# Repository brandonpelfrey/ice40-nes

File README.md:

# ice40-nes
NES implementation in a Lattice Ice40 FPGA

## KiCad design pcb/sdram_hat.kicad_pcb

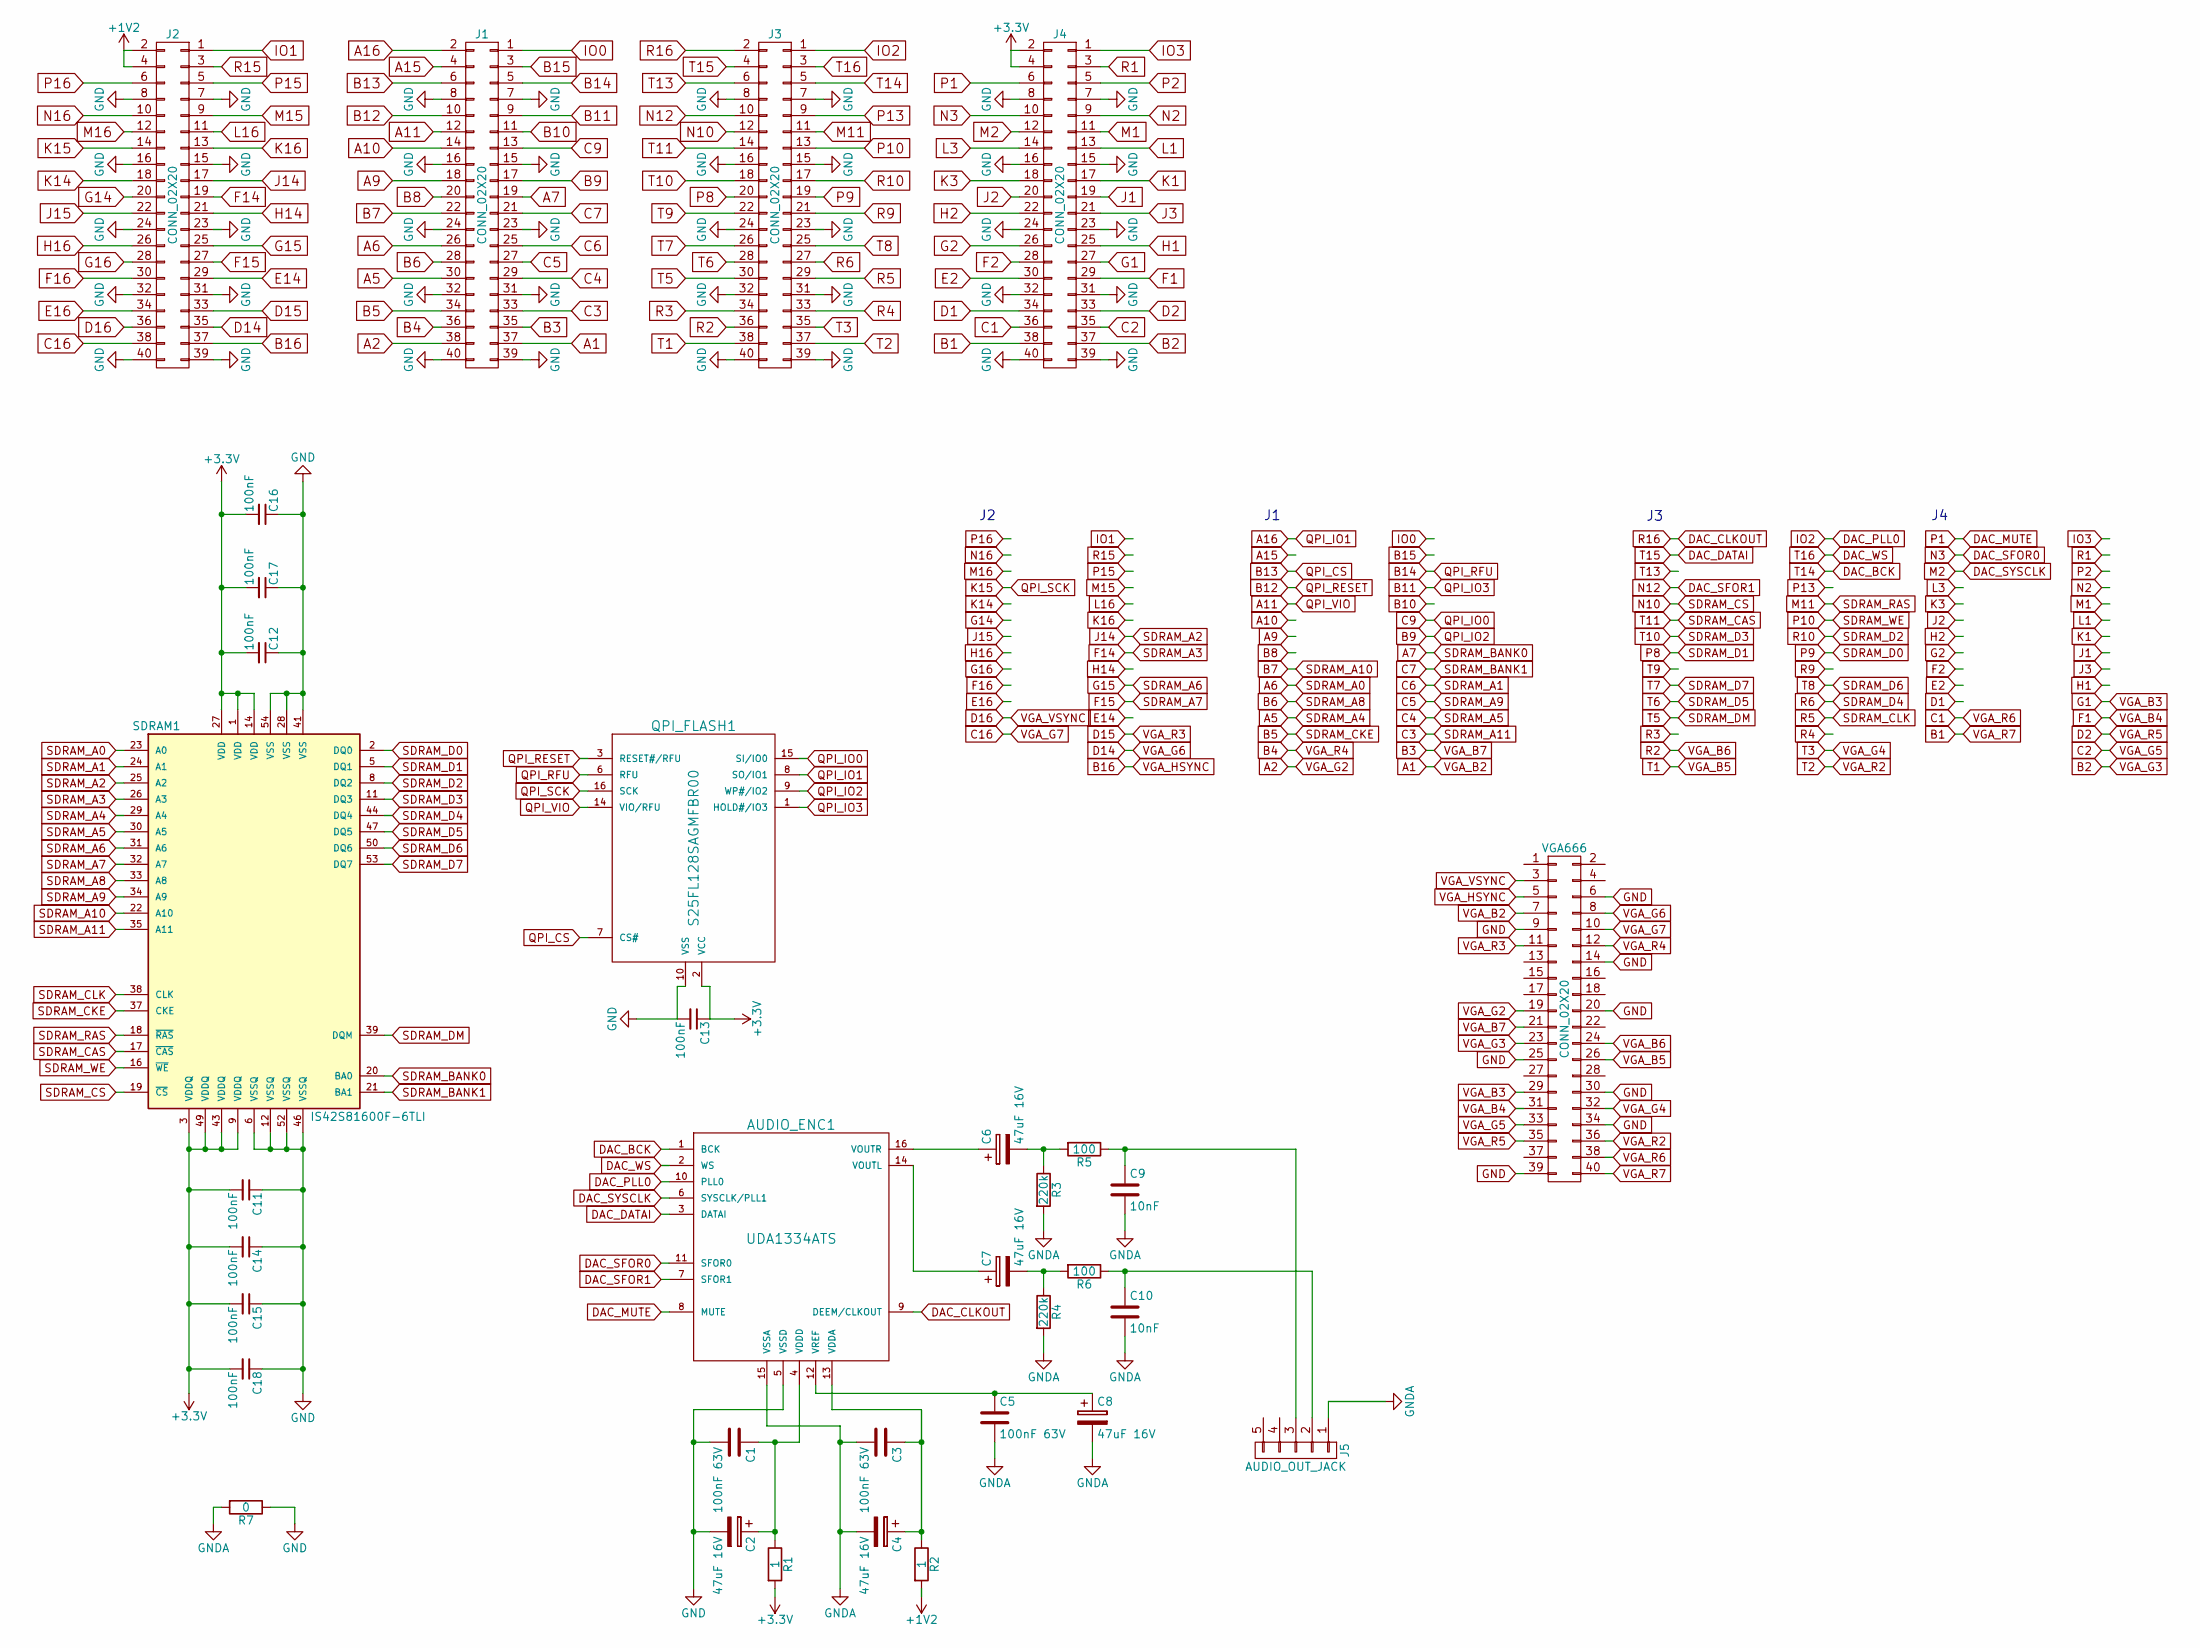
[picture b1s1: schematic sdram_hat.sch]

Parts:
AUDIO_ENC1: UDA1334ATS; SSOP-16_4.4x5.2mm_Pitch0.65mm_ExtendedPad
C1, C3, C5: 100nF 63V; C_0805_HandSoldering
C2, C4, C6, C7, C8: 47uF 16V; CP_Radial_D5.0mm_P2.50mm
C9, C10: 10nF; C_0805_HandSoldering
C11, C12, C13, C14, C15, C16, C17, C18: 100nF; C_0805_HandSoldering
J1, J2, J3, J4: CONN_02X20; Socket_Strip_Straight_2x20_Pitch2.54mm
J5: AUDIO_OUT_JACK; SJ1-352XNG
QPI_FLASH1: S25FL128SAGMFBR00; SOIC-16_7.5x9.9mm_Pitch1.27mm_ExtendedPad
R1, R2: 1; R_0805_HandSoldering
R3, R4: 220k; R_0805_HandSoldering
R5, R6: 100; R_0805_HandSoldering
R7: 0; R_0805_HandSoldering
SDRAM1: IS42S81600F-6TLI; TSOPII-54_10.16x22.22mm_Pitch0.8mm_ExtendedPad
VGA666: CONN_02X20; Pin_Header_Straight_2x20_Pitch2.54mm

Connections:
+1V2: J2.2, J2.4, R2.2
+3V3: C11.2, C12.2, C13.1, C14.2, C15.2, C16.2, C17.2, C18.2, J4.2, J4.4, QPI_FLASH1.2 (VCC), R1.2, SDRAM1.1 (VDD), SDRAM1.3 (VDDQ), SDRAM1.9 (VDDQ), SDRAM1.14 (VDD), SDRAM1.27 (VDD), SDRAM1.43 (VDDQ), SDRAM1.49 (VDDQ)
A1: J1.37, VGA666.7
A2: J1.38, VGA666.19
A5: J1.30, SDRAM1.29 (A4)
A6: J1.26, SDRAM1.23 (A0)
A7: J1.19, SDRAM1.20 (BA0)
A9: J1.18
A10: J1.14
A11: J1.12, QPI_FLASH1.14 (VIO/RFU)
A15: J1.4
A16: J1.2, QPI_FLASH1.8 (SO/IO1)
B1: J4.38, VGA666.40
B2: J4.37, VGA666.23
B3: J1.35, VGA666.21
B4: J1.36, VGA666.12
B5: J1.34, SDRAM1.37 (CKE)
B6: J1.28, SDRAM1.33 (A8)
B7: J1.22, SDRAM1.22 (A10)
B8: J1.20
B9: J1.17, QPI_FLASH1.9 (WP#/IO2)
B10: J1.11
B11: J1.9, QPI_FLASH1.1 (HOLD#/IO3)
B12: J1.10, QPI_FLASH1.3 (RESET#/RFU)
B13: J1.6, QPI_FLASH1.7 (CS#)
B14: J1.5, QPI_FLASH1.6 (RFU)
B15: J1.3
B16: J2.37, VGA666.5
C1: J4.36, VGA666.38
C2: J4.35, VGA666.33
C3: J1.33, SDRAM1.35 (A11)
C4: J1.29, SDRAM1.30 (A5)
C5: J1.27, SDRAM1.34 (A9)
C6: J1.25, SDRAM1.24 (A1)
C7: J1.21, SDRAM1.21 (BA1)
C9: J1.13, QPI_FLASH1.15 (SI/IO0)
C16: J2.38, VGA666.10
D1: J4.34
D2: J4.33, VGA666.35
D14: J2.35, VGA666.8
D15: J2.33, VGA666.11
D16: J2.36, VGA666.3
DAC_BCK: AUDIO_ENC1.1 (BCK), J3.5
DAC_CLKOUT: AUDIO_ENC1.9 (DEEM/CLKOUT), J3.2
DAC_DATAI: AUDIO_ENC1.3 (DATAI), J3.4
DAC_MUTE: AUDIO_ENC1.8 (MUTE), J4.6
DAC_PLL0: AUDIO_ENC1.10 (PLL0), J3.1
DAC_SFOR0: AUDIO_ENC1.11 (SFOR0), J4.10
DAC_SFOR1: AUDIO_ENC1.7 (SFOR1), J3.10
DAC_SYSCLK: AUDIO_ENC1.6 (SYSCLK/PLL1), J4.12
DAC_WS: AUDIO_ENC1.2 (WS), J3.3
E2: J4.30
E14: J2.29
E16: J2.34
F1: J4.29, VGA666.31
F2: J4.28
F14: J2.19, SDRAM1.26 (A3)
F15: J2.27, SDRAM1.32 (A7)
F16: J2.30
G1: J4.27, VGA666.29
G2: J4.26
G14: J2.20
G15: J2.25, SDRAM1.31 (A6)
G16: J2.28
GND: AUDIO_ENC1.5 (VSSD), C1.2, C2.2, C11.1, C12.1, C13.2, C14.1, C15.1, C16.1, C17.1, C18.1, J1.7, J1.8, J1.15, J1.16, J1.23, J1.24, J1.31, J1.32, J1.39, J1.40, J2.7, J2.8, J2.15, J2.16, J2.23, J2.24, J2.31, J2.32, J2.39, J2.40, J3.7, J3.8, J3.15, J3.16, J3.23, J3.24, J3.31, J3.32, J3.39, J3.40, J4.7, J4.8, J4.15, J4.16, J4.23, J4.24, J4.31, J4.32, J4.39, J4.40, QPI_FLASH1.10 (VSS), R7.1, SDRAM1.6 (VSSQ), SDRAM1.12 (VSSQ), SDRAM1.28 (VSS), SDRAM1.41 (VSS), SDRAM1.46 (VSSQ), SDRAM1.52 (VSSQ), SDRAM1.54 (VSS), VGA666.6, VGA666.9, VGA666.14, VGA666.20, VGA666.25, VGA666.30, VGA666.34, VGA666.39
GNDA: AUDIO_ENC1.15 (VSSA), C3.2, C4.2, C5.2, C8.2, C9.2, C10.2, J5.1, R3.2, R4.2, R7.2
H1: J4.25
H2: J4.22
H14: J2.21
H16: J2.26
IO0: J1.1
IO1: J2.1
IO3: J4.1
J1: J4.19
J2: J4.20
J3: J4.21
J14: J2.17, SDRAM1.25 (A2)
J15: J2.22
K1: J4.17
K3: J4.18
K14: J2.18
K15: J2.14, QPI_FLASH1.16 (SCK)
K16: J2.13
L1: J4.13
L3: J4.14
L16: J2.11
M1: J4.11
M11: J3.11, SDRAM1.18 (~RAS~)
M15: J2.9
M16: J2.12
N2: J4.9
N10: J3.12, SDRAM1.19 (~CS~)
N16: J2.10
unnamed: AUDIO_ENC1.4 (VDDD), C1.1, C2.1, R1.1
unnamed: AUDIO_ENC1.12 (VREF), C5.1, C8.1
unnamed: AUDIO_ENC1.13 (VDDA), C3.1, C4.1, R2.1
unnamed: AUDIO_ENC1.14 (VOUTL), C7.1
unnamed: AUDIO_ENC1.16 (VOUTR), C6.1
unnamed: C6.2, R3.1, R5.2
unnamed: C7.2, R4.1, R6.2
unnamed: C9.1, J5.3, R5.1
unnamed: C10.1, J5.2, R6.1
P2: J4.5
P8: J3.20, SDRAM1.5 (DQ1)
P9: J3.19, SDRAM1.2 (DQ0)
P10: J3.13, SDRAM1.16 (~WE~)
P13: J3.9
P15: J2.5
P16: J2.6
R1: J4.3
R2: J3.36, VGA666.24
R3: J3.34
R4: J3.33
R5: J3.29, SDRAM1.38 (CLK)
R6: J3.27, SDRAM1.44 (DQ4)
R9: J3.21
R10: J3.17, SDRAM1.8 (DQ2)
R15: J2.3
SDRAM_CAS: J3.14, SDRAM1.17 (~CAS~)
SDRAM_D3: J3.18, SDRAM1.11 (DQ3)
SDRAM_D5: J3.28, SDRAM1.47 (DQ5)
SDRAM_D6: J3.25, SDRAM1.50 (DQ6)
SDRAM_D7: J3.26, SDRAM1.53 (DQ7)
SDRAM_DM: J3.30, SDRAM1.39 (DQM)
T1: J3.38, VGA666.26
T2: J3.37, VGA666.36
T3: J3.35, VGA666.32
T9: J3.22
T13: J3.6

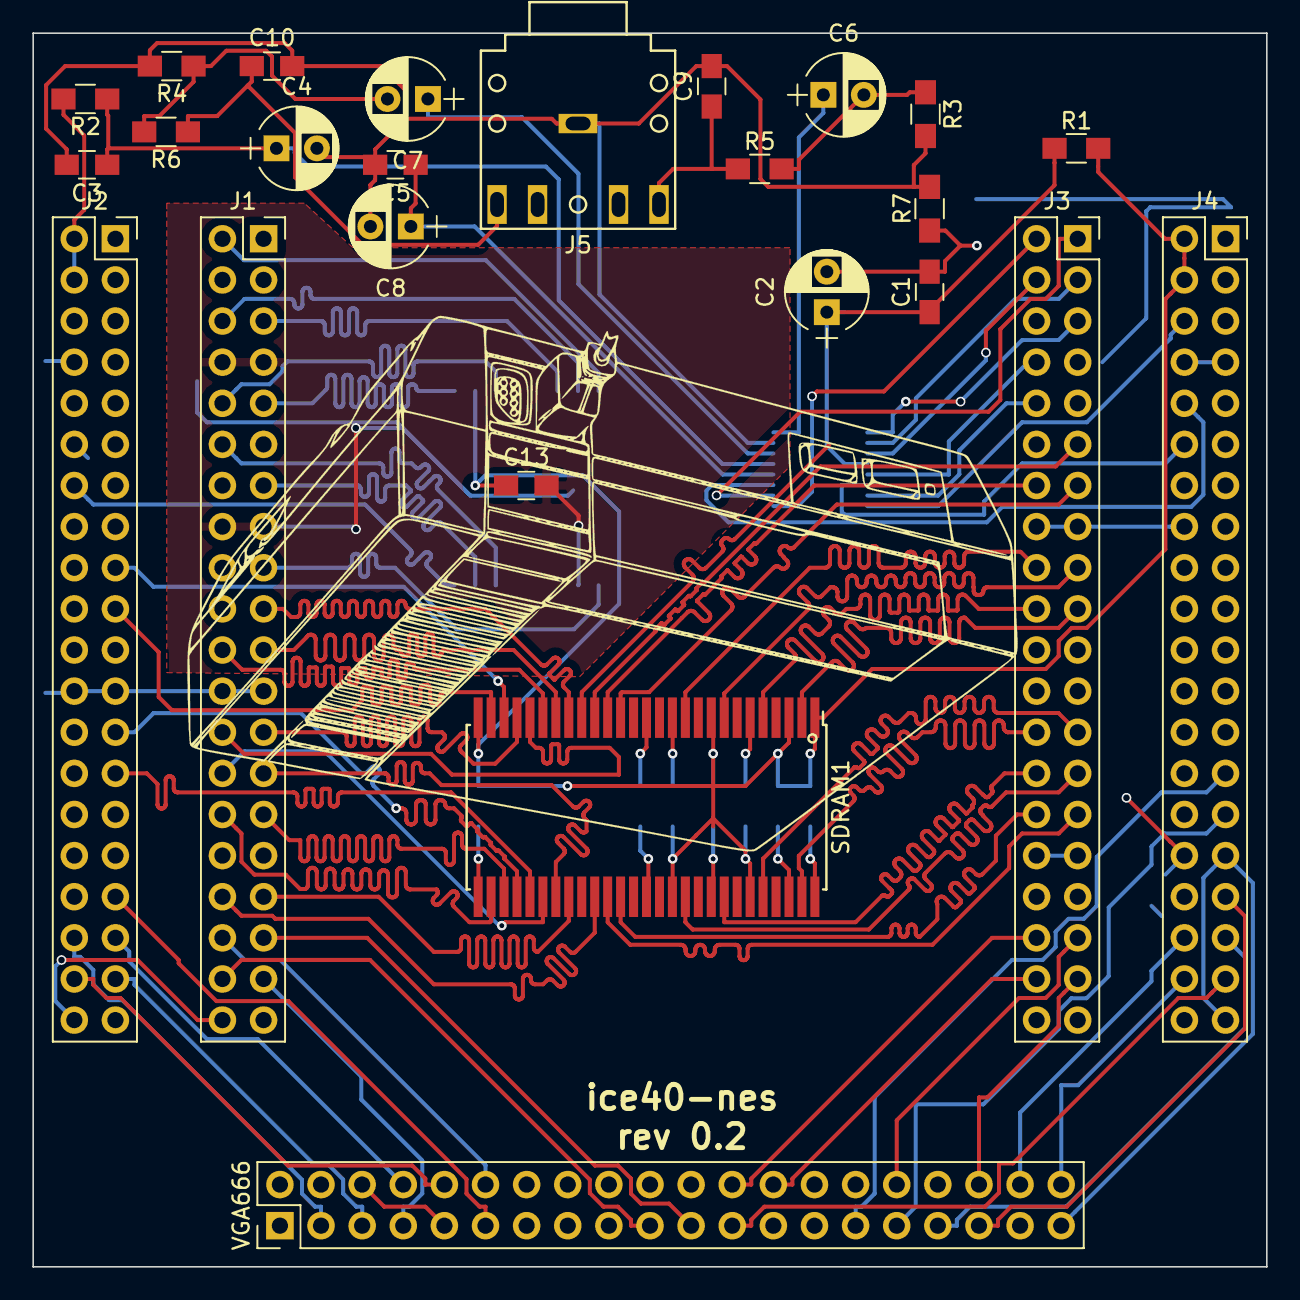
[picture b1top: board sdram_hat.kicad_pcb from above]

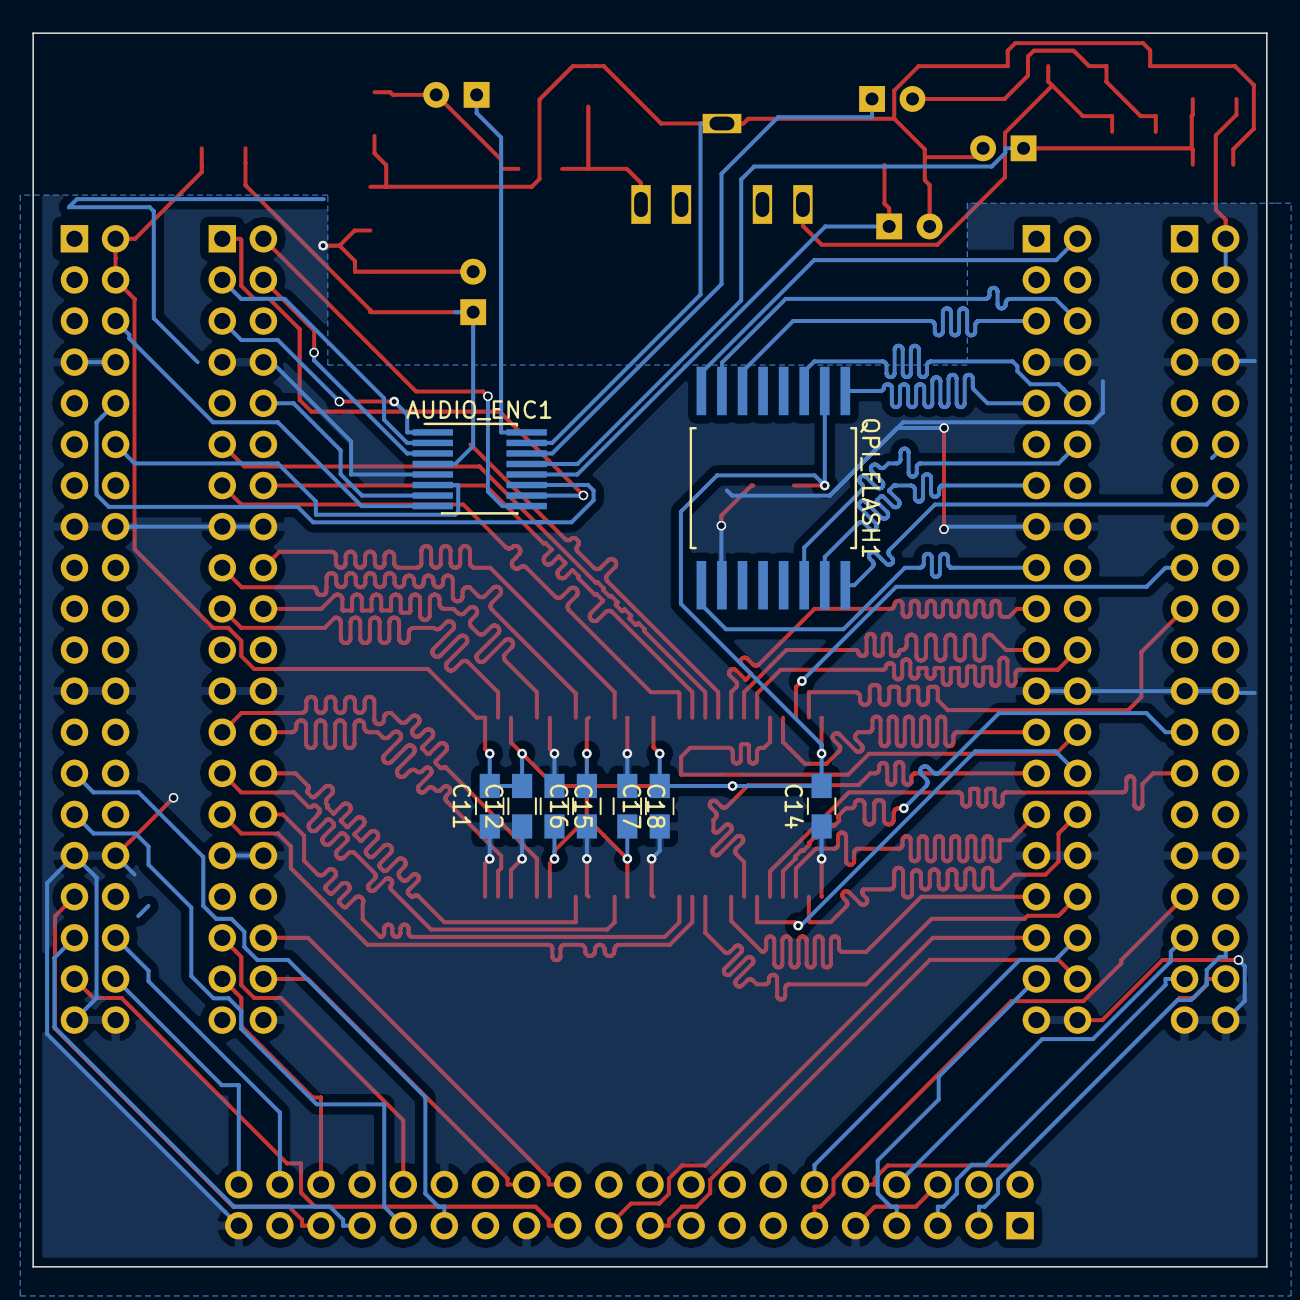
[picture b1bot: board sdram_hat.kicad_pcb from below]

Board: 2 copper layers, 76.2 x 76.2 mm, 34 parts (9 on the bottom side), 80 nets.

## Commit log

2017-08-18 Update LICENSE
2017-08-18 Add initial framework for building
2017-08-20 Refactor Makefile and add -noautowire to yosys options
2017-08-21 Adding ClockMaster, VGA Encoder, and preliminary Hex Display for a 64-bit counter
2017-08-21 Adding timing target to computer critical path length/speed
2017-08-22 Fixed bug in mod_hex_display font bitmap
2017-08-22 Adding additional modules and standardizing in/out/w_
2017-08-22 Minor cleanup of mod_hex_display (latch logic + move down)
2017-08-22 Improve hex font glyph sharpness
2017-08-23 Add NES controller module and hook up controller 0
2017-08-25 Initial commit of NESHAT
2017-08-26 Some additional layout work on PCB
2017-08-26 Add footprint for SJ1-352XNG
2017-08-27 Add NES connector footprint
2017-08-27 Added more pin definitions and progress on board layout
2017-08-27 Added TH passives, analog+digital ground planes, some autorouting stuff.
2017-08-27 Cleanup VGA module, add grid display
2017-08-27 Fixing AGND on a few DAC components
2017-08-27 Force hex display to infer BRAM
2017-08-27 Add extended pad footprints for PCB SMD chips
2017-08-27 Moved to SMD, moving components to back side, added some decoupling
2017-08-28 Switch out larger footprints, minor pinout tweaks
2017-08-28 Add a bunch of decoupling caps to PCB
2017-08-28 Fix footprint size for SOIC package QPI flash
2017-08-28 Attempt #2 at previous
2017-08-28 Fix footprint cuts for audio jack
2017-08-29 Length match QPI flash and SDRAM traces
2017-08-29 Very misalign. Wow. Much fix.
2017-09-01 Adding best guess at sdram controller
2017-09-01 Fixes to sdram controller
2018-08-26 Updated NES-Hat PCB to rev 2
